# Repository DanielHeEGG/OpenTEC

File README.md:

# OpenTEC
OpenTEC is a low-cost, DIY temperature controller. Designed to be used as a controller for temperature chambers.

The controller board works by taking in temperature readings and driving thermoelectric coolers (TEC) in order to control the temperature inside the chamber.

This can be also used as a controller for **terribly ineffcient** DIY fridges and air conditioners.

This project is currently a work in progress.

## Features
- Built-in LCD screen and user interface.
- Up to 4 analog temperature sensor inputs.
- I2C port for peripherals.
- Discrete H-bridge driving currents up to 8 amps.
- All SMD components selected to be assembled by [JLCPCB](https://jlcpcb.com/).

## Structure
`Hardware/` - PCB source files, designed with [KiCAD](https://kicad.org/).

`Fabrication/` - Exported fabrication files (Gerber, BOM, POS).

`Firmware/` - Firmware source code, written with [PlatformIO IDE](https://platformio.org/).

## License
- The hardware portion of the project (everything under `Hardware/` and `Fabrication/`) is licensed under the [CERN Open Hardware Licence](https://cern-ohl.web.cern.ch/home).
- The firmware portion of the project (everything under `Firmware/`, with exceptions, see below) is licensed under the [3-Clause BSD License](https://opensource.org/licenses/BSD-3-Clause).

#### Exceptions
- [FreeRTOSConfig.h](Firmware/include/FreeRTOSConfig.h) `Copyright 2017 Amazon.com, Inc. or its affiliates.`
- [stm32f1xx_hal_conf.h](Firmware/include/stm32f1xx_hal_conf.h) `Copyright 2017 STMicroelectronics.`

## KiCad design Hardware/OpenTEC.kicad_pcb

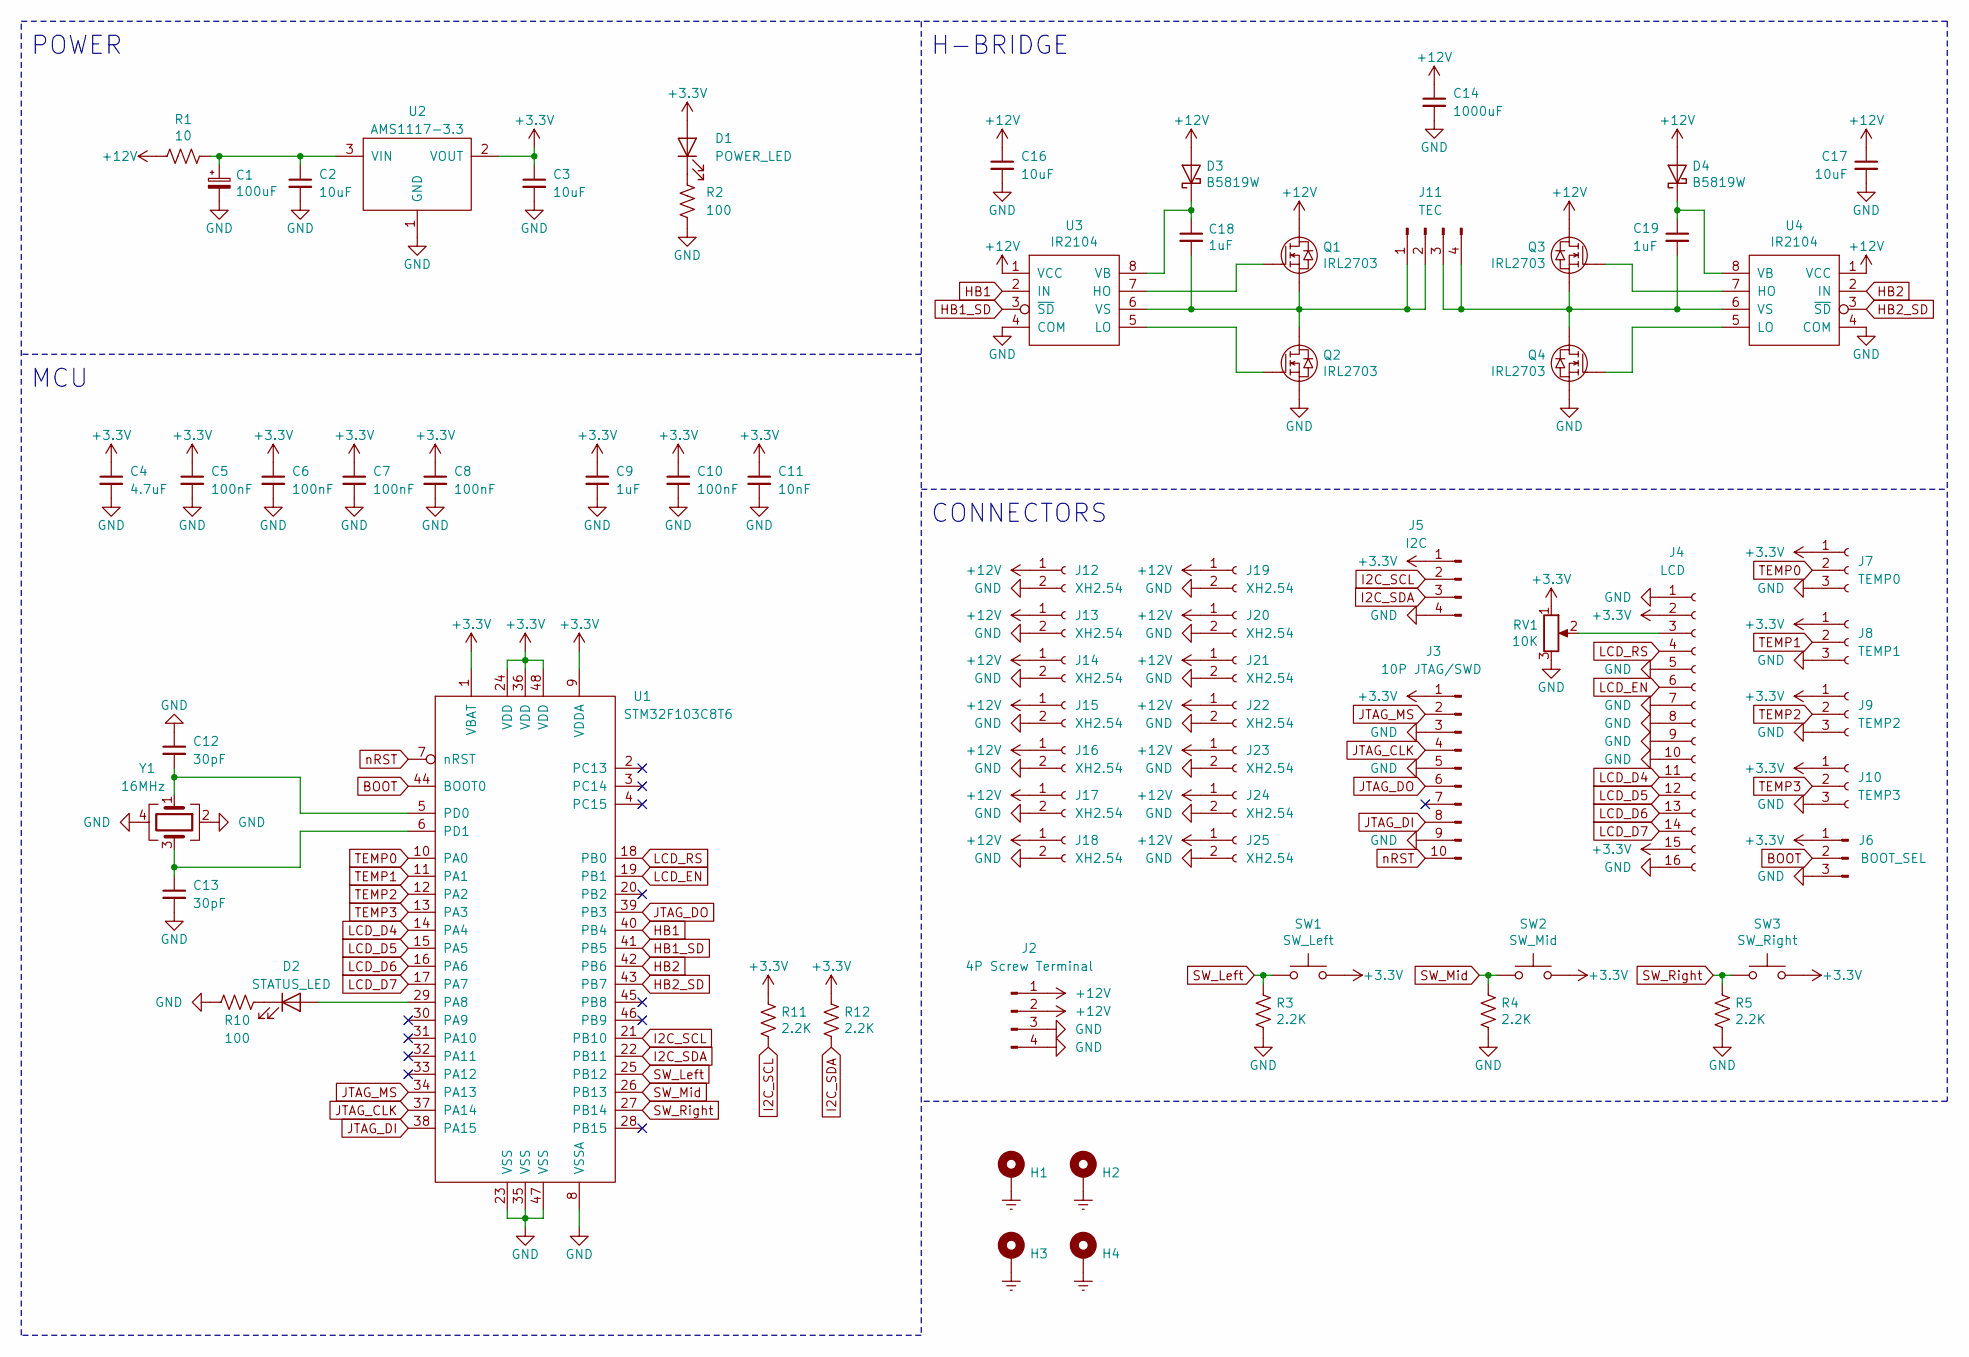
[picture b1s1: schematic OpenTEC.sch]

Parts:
C1: 100uF; CP_Elec_6.3x5.3
C2, C3, C16, C17: 10uF; C_0805_2012Metric
C4: 4.7uF; C_0805_2012Metric
C5, C6, C7, C8, C10: 100nF; C_0402_1005Metric
C9, C18, C19: 1uF; C_0805_2012Metric
C11: 10nF; C_0402_1005Metric
C12, C13: 30pF; C_0603_1608Metric
C14: 1000uF; CP_Radial_D13.0mm_P5.00mm
D1: POWER_LED; LED_0603_1608Metric
D2: STATUS_LED; LED_0603_1608Metric
D3, D4: B5819W; D_SOD-123
H1, H2, H3, H4: MountingHole_3.2mm_M3_Pad_Via
J2: 4P Screw Terminal; TerminalBlock_bornier-4_P5.08mm
J3: 10P JTAG/SWD; PinHeader_2x05_P2.54mm_Vertical
J4: LCD; PinSocket_1x16_P2.54mm_Vertical
J5: I2C; PinHeader_1x04_P2.54mm_Vertical
J6: BOOT_SEL; PinHeader_1x03_P2.54mm_Vertical
J7: TEMP0; PinSocket_1x03_P2.54mm_Vertical
J8: TEMP1; PinSocket_1x03_P2.54mm_Vertical
J9: TEMP2; PinSocket_1x03_P2.54mm_Vertical
J10: TEMP3; PinSocket_1x03_P2.54mm_Vertical
J11: TEC; TerminalBlock_bornier-4_P5.08mm
J12, J13, J14, J15, J16, J17, J18, J19, J20, J21, J22, J23, J24, J25: XH2.54; JST_XH_B2B-XH-A_1x02_P2.50mm_Vertical
Q1, Q2, Q3, Q4: IRL2703; TO-220-3_Vertical
R1: 10; R_Axial_Power_L20.0mm_W6.4mm_P22.40mm
R2, R10: 100; R_0402_1005Metric
R3, R4, R5, R11, R12: 2.2K; R_0402_1005Metric
RV1: 10K; Potentiometer_Bourns_3386P_Vertical
SW1: SW_Left; SW_PUSH_6mm
SW2: SW_Mid; SW_PUSH_6mm
SW3: SW_Right; SW_PUSH_6mm
U1: STM32F103C8T6; LQFP-48_7x7mm_P0.5mm
U2: AMS1117-3.3; SOT-223-3_TabPin2
U3, U4: IR2104; SOIC-8_3.9x4.9mm_P1.27mm
Y1: 16MHz; Crystal_SMD_3225-4Pin_3.2x2.5mm

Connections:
+3V3: C3.1, C4.1, C5.1, C6.1, C7.1, C8.1, C9.1, C10.1, C11.1, D1.2 (A), J3.1, J4.2, J4.15, J5.1, J6.1, J7.1, J8.1, J9.1, J10.1, R11.1, R12.1, RV1.1, SW1.2, SW2.2, SW3.2, U1.1 (VBAT), U1.9 (VDDA), U1.24 (VDD), U1.36 (VDD), U1.48 (VDD), U2.2 (VOUT)
+12V: C14.1, C16.1, C17.1, D3.2 (A), D4.2 (A), J2.1, J2.2, J12.1, J13.1, J14.1, J15.1, J16.1, J17.1, J18.1, J19.1, J20.1, J21.1, J22.1, J23.1, J24.1, J25.1, Q1.2, Q3.2, R1.2, U3.1 (VCC), U4.1 (VCC)
BOOT: J6.2, U1.44 (BOOT0)
Earth: H1.1, H2.1, H3.1, H4.1
GND: C1.2, C2.2, C3.2, C4.2, C5.2, C6.2, C7.2, C8.2, C9.2, C10.2, C11.2, C12.1, C13.2, C14.2, C16.2, C17.2, J2.3, J2.4, J3.3, J3.5, J3.9, J4.1, J4.5, J4.7, J4.8, J4.9, J4.10, J4.16, J5.4, J6.3, J7.3, J8.3, J9.3, J10.3, J12.2, J13.2, J14.2, J15.2, J16.2, J17.2, J18.2, J19.2, J20.2, J21.2, J22.2, J23.2, J24.2, J25.2, Q2.3, Q4.3, R2.2, R3.2, R4.2, R5.2, R10.2, RV1.3, U1.8 (VSSA), U1.23 (VSS), U1.35 (VSS), U1.47 (VSS), U2.1 (GND), U3.4 (COM), U4.4 (COM), Y1.2, Y1.4
HB1: U1.40 (PB4), U3.2 (IN)
HB1_SD: U1.41 (PB5), U3.3 (~SD)
HB2: U1.42 (PB6), U4.2 (IN)
HB2_SD: U1.43 (PB7), U4.3 (~SD)
I2C_SCL: J5.2, R11.2, U1.21 (PB10)
I2C_SDA: J5.3, R12.2, U1.22 (PB11)
JTAG_CLK: J3.4, U1.37 (PA14)
JTAG_DI: J3.8, U1.38 (PA15)
JTAG_DO: J3.6, U1.39 (PB3)
JTAG_MS: J3.2, U1.34 (PA13)
LCD_D4: J4.11, U1.14 (PA4)
LCD_D5: J4.12, U1.15 (PA5)
LCD_D6: J4.13, U1.16 (PA6)
LCD_D7: J4.14, U1.17 (PA7)
LCD_EN: J4.6, U1.19 (PB1)
LCD_RS: J4.4, U1.18 (PB0)
unnamed: C1.1, C2.1, R1.1, U2.3 (VIN)
unnamed: C12.2, U1.5 (PD0), Y1.1
unnamed: C13.1, U1.6 (PD1), Y1.3
unnamed: C18.1, D3.1 (K), U3.8 (VB)
unnamed: C18.2, J11.1, J11.2, Q1.3, Q2.2, U3.6 (VS)
unnamed: C19.1, D4.1 (K), U4.8 (VB)
unnamed: C19.2, J11.3, J11.4, Q3.3, Q4.2, U4.6 (VS)
unnamed: D1.1 (K), R2.1
unnamed: D2.1 (K), R10.1
unnamed: D2.2 (A), U1.29 (PA8)
unnamed: J4.3, RV1.2
unnamed: Q1.1, U3.7 (HO)
unnamed: Q2.1, U3.5 (LO)
unnamed: Q3.1, U4.7 (HO)
unnamed: Q4.1, U4.5 (LO)
SW_Left: R3.1, SW1.1, U1.25 (PB12)
SW_Mid: R4.1, SW2.1, U1.26 (PB13)
SW_Right: R5.1, SW3.1, U1.27 (PB14)
TEMP0: J7.2, U1.10 (PA0)
TEMP1: J8.2, U1.11 (PA1)
TEMP2: J9.2, U1.12 (PA2)
TEMP3: J10.2, U1.13 (PA3)
nRST: J3.10, U1.7 (nRST)

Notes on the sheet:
POWER
MCU
H-BRIDGE
CONNECTORS

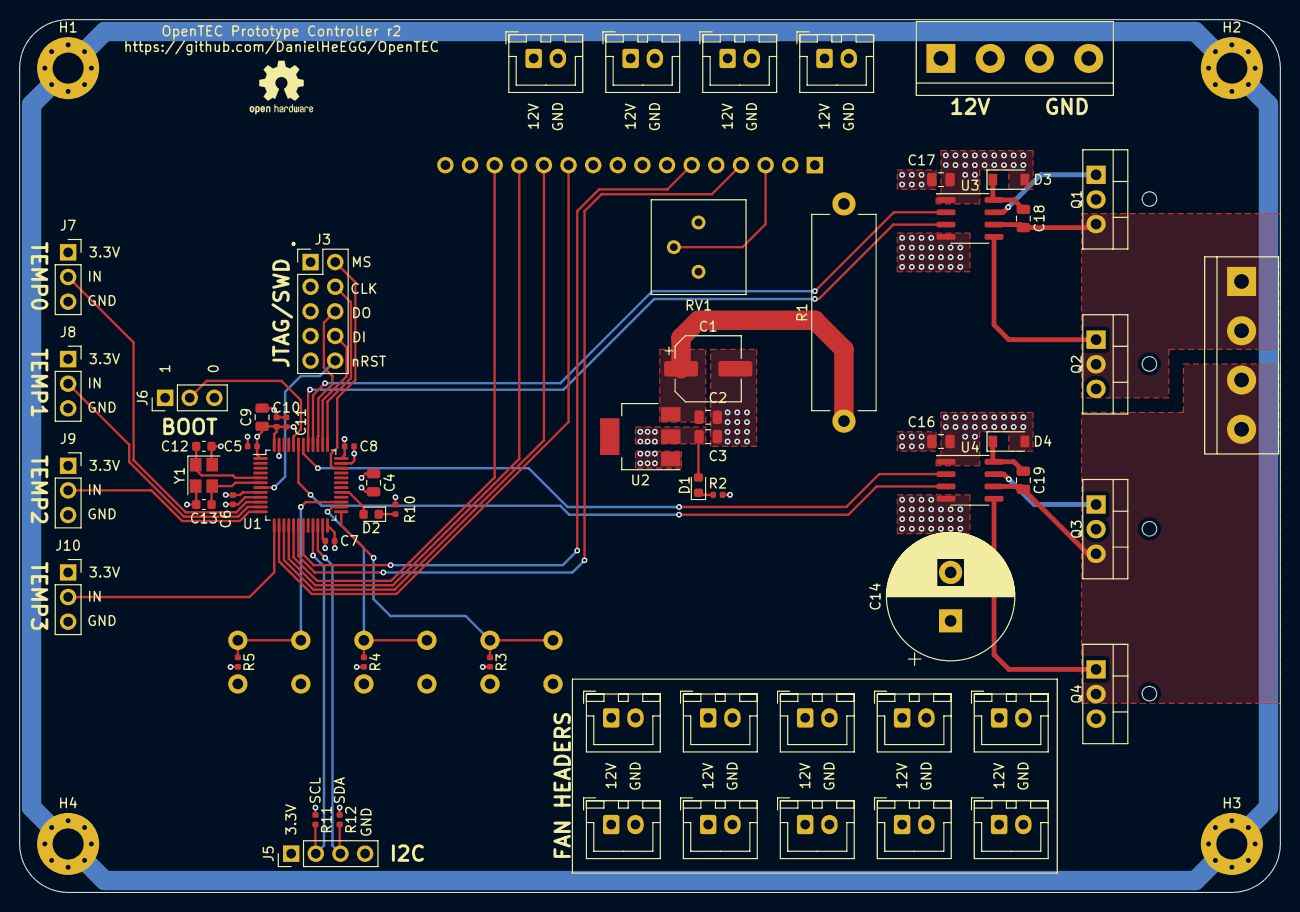
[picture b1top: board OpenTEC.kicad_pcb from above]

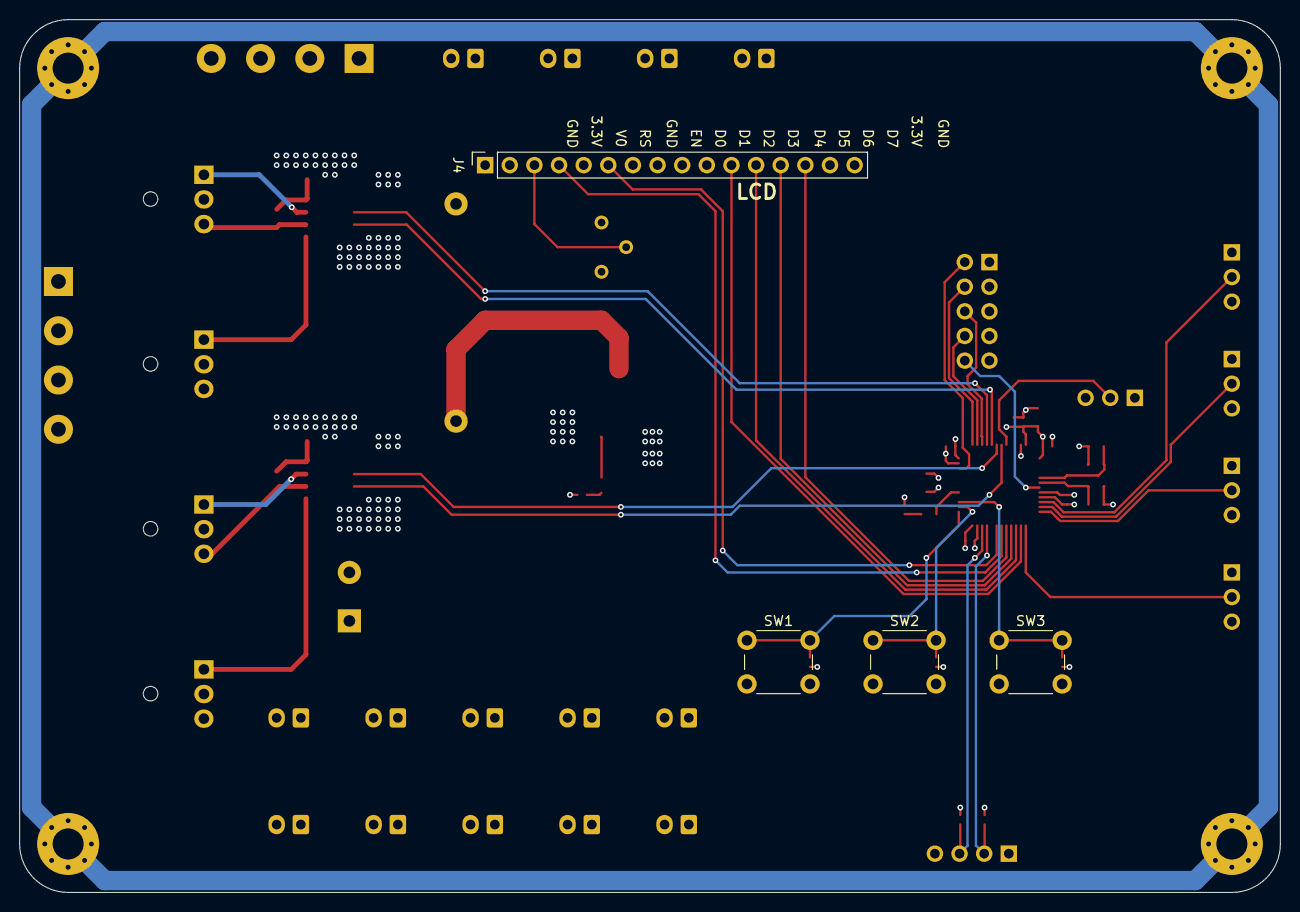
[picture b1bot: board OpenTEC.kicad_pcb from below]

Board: 4 copper layers, 130.0 x 90.0 mm, 71 parts (4 on the bottom side), 44 nets.

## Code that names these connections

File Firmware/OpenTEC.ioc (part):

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Mcu.Name=STM32F103C(8-B)Tx
Mcu.Package=LQFP48
Mcu.UserName=STM32F103C8Tx
PA0-WKUP.GPIOParameters=GPIO_Label
PA0-WKUP.GPIO_Label=TEMP0
PA0-WKUP.Signal=ADCx_IN0
PA1.GPIOParameters=GPIO_Label
PA1.GPIO_Label=TEMP1
PA1.Signal=ADCx_IN1
PA13.Mode=JTAG_4_pins
PA13.Signal=SYS_JTMS-SWDIO
PA14.Mode=JTAG_4_pins
PA14.Signal=SYS_JTCK-SWCLK
PA15.Mode=JTAG_4_pins
PA15.Signal=SYS_JTDI
PA2.GPIOParameters=GPIO_Label
PA2.GPIO_Label=TEMP2
PA2.Signal=ADCx_IN2
PA3.GPIOParameters=GPIO_Label
PA3.GPIO_Label=TEMP3
PA3.Signal=ADCx_IN3
PA4.GPIOParameters=GPIO_Label
PA4.GPIO_Label=LCD_D4
PA4.Signal=GPIO_Output
PA5.GPIOParameters=GPIO_Label
PA5.GPIO_Label=LCD_D5
PA5.Signal=GPIO_Output
PA6.GPIOParameters=GPIO_Label
PA6.GPIO_Label=LCD_D6
PA6.Signal=GPIO_Output
PA7.GPIOParameters=GPIO_Label
PA7.GPIO_Label=LCD_D7
PA7.Signal=GPIO_Output
PA8.GPIOParameters=GPIO_Label
PA8.GPIO_Label=STATUS_LED
PA8.Signal=GPIO_Output
PB0.GPIOParameters=GPIO_Label
PB0.GPIO_Label=LCD_RS
PB0.Signal=GPIO_Output
PB1.GPIOParameters=GPIO_Label
PB1.GPIO_Label=LCD_EN
PB1.Signal=GPIO_Output
PB10.Mode=I2C
PB10.Signal=I2C2_SCL
PB11.Mode=I2C
PB11.Signal=I2C2_SDA
PB12.GPIOParameters=GPIO_Label
PB12.GPIO_Label=SW_L
PB12.Signal=GPXTI12
PB13.GPIOParameters=GPIO_Label
PB13.GPIO_Label=SW_M
PB13.Signal=GPXTI13
PB14.GPIOParameters=GPIO_Label
PB14.GPIO_Label=SW_R
PB14.Signal=GPXTI14
PB3.Mode=JTAG_4_pins
PB3.Signal=SYS_JTDO-TRACESWO
PB4.GPIOParameters=GPIO_Label
PB4.GPIO_Label=HB1
PB4.Signal=S_TIM3_CH1
PB5.GPIOParameters=GPIO_Label
PB5.GPIO_Label=HB1_SD
PB5.Signal=GPIO_Output
PB6.GPIOParameters=GPIO_Label
PB6.GPIO_Label=HB2
PB6.Signal=S_TIM4_CH1
PB7.GPIOParameters=GPIO_Label
PB7.GPIO_Label=HB2_SD
PB7.Signal=GPIO_Output
PD0-OSC_IN.Mode=HSE-External-Oscillator
PD0-OSC_IN.Signal=RCC_OSC_IN
PD1-OSC_OUT.Mode=HSE-External-Oscillator
PD1-OSC_OUT.Signal=RCC_OSC_OUT
RCC.HSEDivPLL=RCC_HSE_PREDIV_DIV2
RCC.HSE_VALUE=16000000
RCC.SYSCLKFreq_VALUE=72000000
RCC.SYSCLKSource=RCC_SYSCLKSOURCE_PLLCLK
board=custom

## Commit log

2021-01-24 Finish schematic
2021-01-25 Add I2C connector
2021-01-25 Ground unused pins on LCD connector
2021-01-25 Add temperature sensor connectors
2021-01-25 Add fan headers
2021-01-25 Add footprints to components
2021-01-25 Finish PCB layout, export fabrication files
2021-01-26 Change H-bridge design
2021-01-27 Fix USB Micro B connector footprint
2021-02-03 Add BFC to H-bridge
2021-02-03 Remove unused USB port and 5V LDO
2021-02-04 Add RC filter to 3.3V LDO input
2021-02-04 Removed unused symbols
2021-02-04 Add control push buttons
2021-02-06 Fix H-bridge supply voltage
2021-02-17 Add more vias to H-bridge
2021-03-04 Add firmware structure
2021-03-05 Generate framework code with STM32CubeMX
2021-03-05 Update CubeMX config file to match firmware
2021-03-05 Add LICENSE and README
2021-03-05 Add LCD functions
